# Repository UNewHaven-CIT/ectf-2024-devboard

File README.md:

# UNewHaven 2024 eCTF
### Rev A

This is a daughterboard for the MAX78000FT development board, designed for the 2024 eCTF competition.

This was partially inspired by MITRE's own board design, and from a joke gone too far (the leds are what started it all).

# Features
- As the competition has 3 interconnected boards, this design provisions for side-interconnects
- Independent and chain-able WS2812B LEDs on the top of the board, for some true ectf gaming
- Expandable IO for MAX78000FT board
- SMA monitoring for a selection of voltage lines

# License
This project is licensed under GPLv3.

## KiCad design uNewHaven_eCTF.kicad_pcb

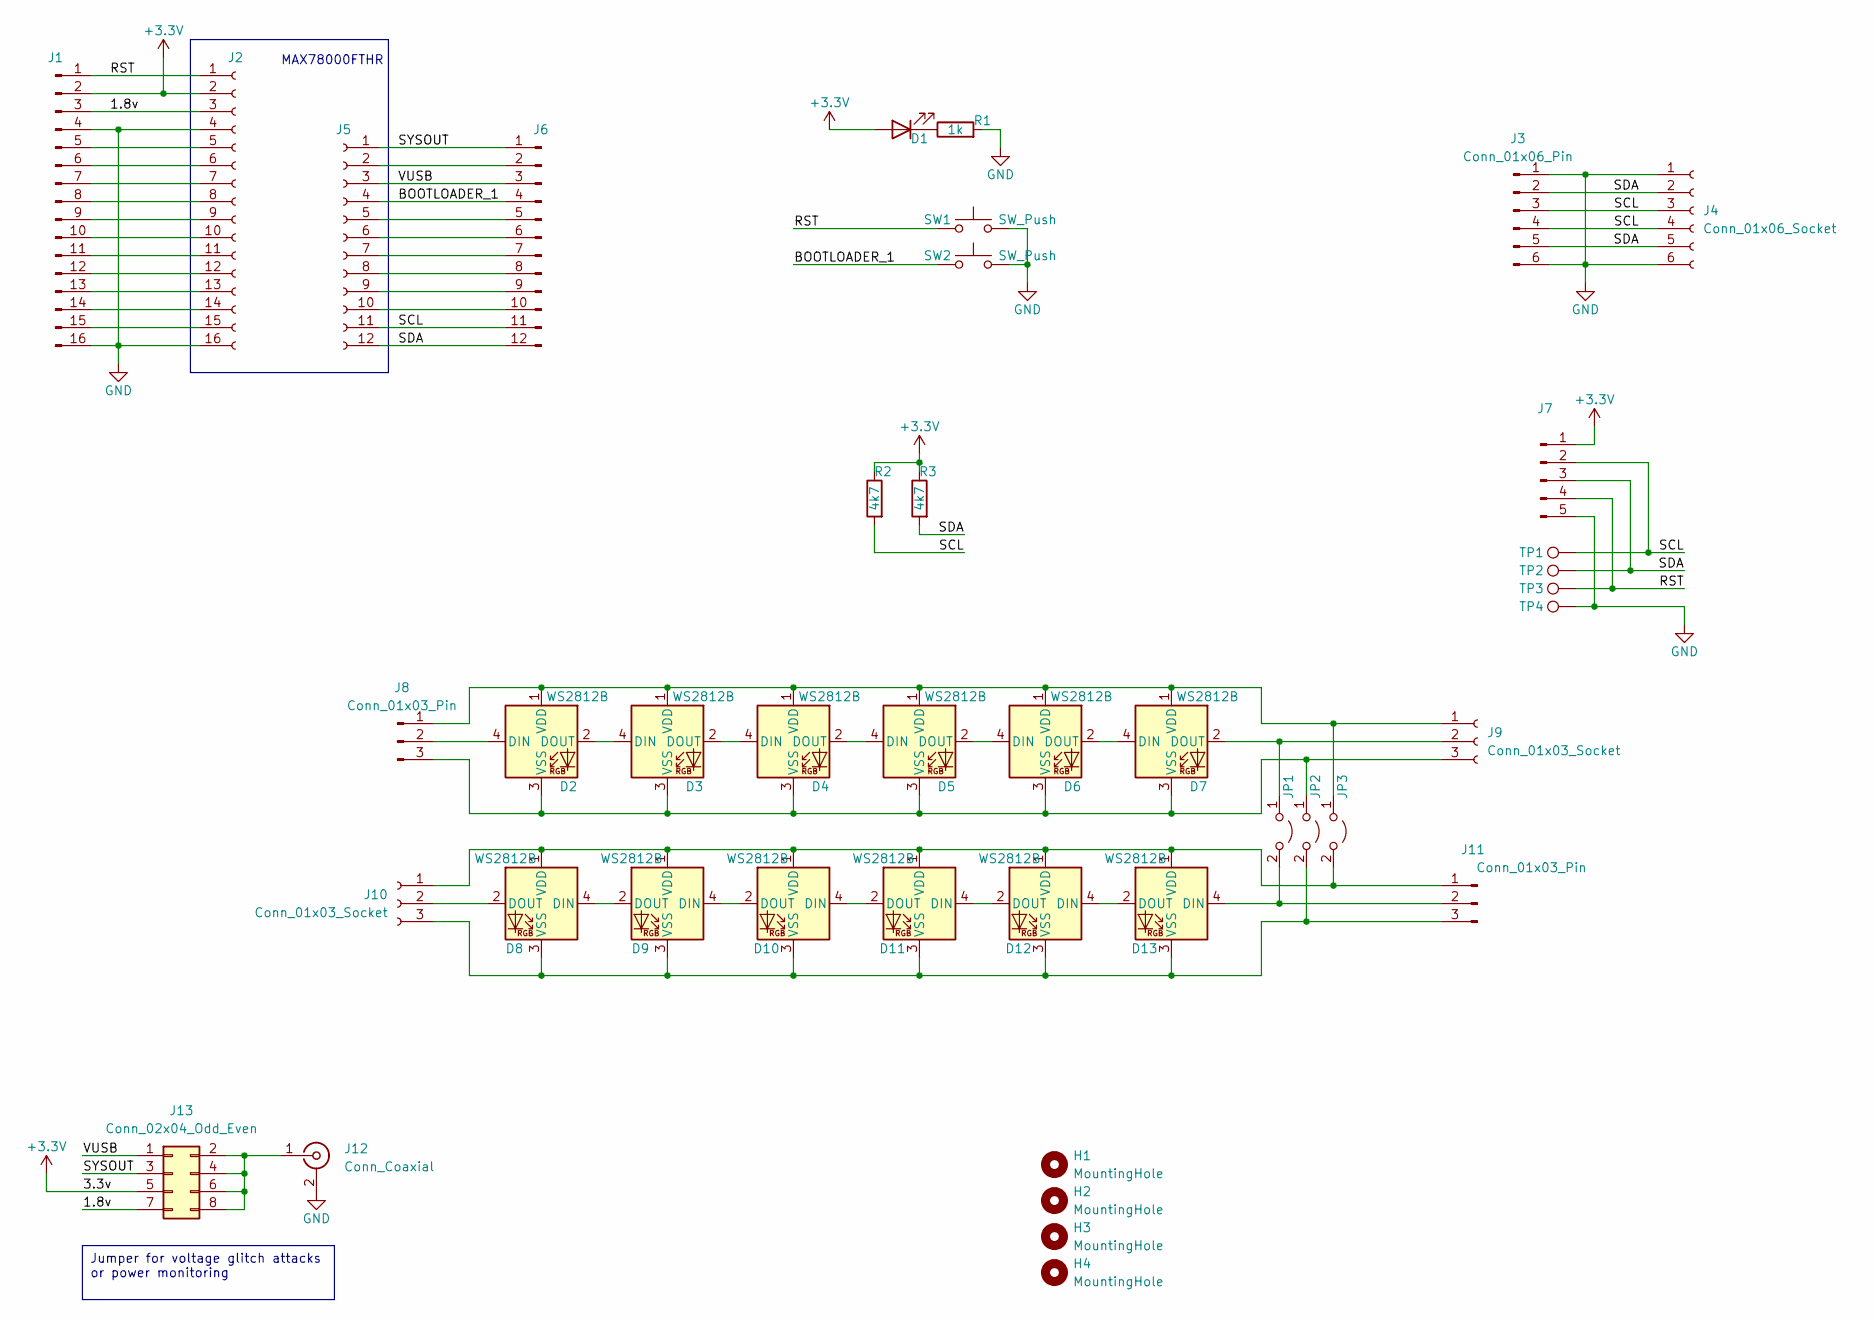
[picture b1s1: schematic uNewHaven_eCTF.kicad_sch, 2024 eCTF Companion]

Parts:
D1: LED; D_1206_3216Metric_Pad1.42x1.75mm_HandSolder
D2, D3, D4, D5, D6, D7, D8, D9, D10, D11, D12, D13: WS2812B; LED_WS2812B_PLCC4_5.0x5.0mm_P3.2mm
H1, H2, H3, H4: MountingHole; MountingHole_3.2mm_M3_DIN965
J1: Conn_01x16_Pin; PinHeader_1x16_P2.54mm_Vertical
J2: Conn_01x16_Socket; PinSocket_1x16_P2.54mm_Vertical
J3: Conn_01x06_Pin; PinHeader_1x06_P2.54mm_Horizontal
J4: Conn_01x06_Socket; PinSocket_1x06_P2.54mm_Horizontal
J5: Conn_01x12_Socket; PinSocket_1x12_P2.54mm_Vertical
J6: Conn_01x12_Pin; PinHeader_1x12_P2.54mm_Vertical
J7: Conn_01x05_Pin; PinHeader_1x05_P2.54mm_Vertical
J8, J11: Conn_01x03_Pin; PinHeader_1x03_P2.54mm_Horizontal
J9, J10: Conn_01x03_Socket; PinSocket_1x03_P2.54mm_Horizontal
J12: Conn_Coaxial; SMA_Amphenol_132291_Vertical
J13: Conn_02x04_Odd_Even; PinHeader_2x04_P2.54mm_Vertical
JP1, JP2, JP3: Jumper_2_Open; R_0805_2012Metric_Pad1.20x1.40mm_HandSolder
R1: 1k; R_0805_2012Metric_Pad1.20x1.40mm_HandSolder
R2, R3: 4k7; R_0805_2012Metric_Pad1.20x1.40mm_HandSolder
SW1, SW2: SW_Push; SW_PUSH_6mm
TP1, TP2, TP3, TP4: TestPoint; TestPoint_Keystone_5005-5009_Compact

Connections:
+3.3V: D1.2 (A), J1.2, J2.2, J7.1, J13.5, R2.1, R3.1
/1.8v: J1.3, J2.3, J13.7
/BOOTLOADER_1: J5.4, J6.4, SW2.1
/RST: J1.1, J2.1, J7.4, SW1.1, TP3.1
/SCL: J3.3, J3.4, J4.3, J4.4, J5.11, J6.11, J7.2, R2.2, TP1.1
/SDA: J3.2, J3.5, J4.2, J4.5, J5.12, J6.12, J7.3, R3.2, TP2.1
/SYSOUT: J5.1, J6.1, J13.3
/VUSB: J5.3, J6.3, J13.1
GND: J1.4, J1.16, J2.4, J2.16, J3.1, J3.6, J4.1, J4.6, J7.5, J12.2 (Ext), R1.2, SW1.2, SW2.2, TP4.1
unnamed: D1.1 (K), R1.1
unnamed: D2.4 (DIN), J8.2
unnamed: D2.2 (DOUT), D3.4 (DIN)
unnamed: D2.1 (VDD), D3.1 (VDD), D4.1 (VDD), D5.1 (VDD), D6.1 (VDD), D7.1 (VDD), J8.1, J9.1, JP3.1 (A)
unnamed: D2.3 (VSS), D3.3 (VSS), D4.3 (VSS), D5.3 (VSS), D6.3 (VSS), D7.3 (VSS), J8.3, J9.3, JP2.1 (A)
unnamed: D3.2 (DOUT), D4.4 (DIN)
unnamed: D4.2 (DOUT), D5.4 (DIN)
unnamed: D5.2 (DOUT), D6.4 (DIN)
unnamed: D6.2 (DOUT), D7.4 (DIN)
unnamed: D7.2 (DOUT), J9.2, JP1.1 (A)
unnamed: D8.4 (DIN), D9.2 (DOUT)
unnamed: D8.2 (DOUT), J10.2
unnamed: D10.4 (DIN), D11.2 (DOUT)
unnamed: D9.4 (DIN), D10.2 (DOUT)
unnamed: D8.1 (VDD), D9.1 (VDD), D10.1 (VDD), D11.1 (VDD), D12.1 (VDD), D13.1 (VDD), J10.1, J11.1, JP3.2 (B)
unnamed: D8.3 (VSS), D9.3 (VSS), D10.3 (VSS), D11.3 (VSS), D12.3 (VSS), D13.3 (VSS), J10.3, J11.3, JP2.2 (B)
unnamed: D11.4 (DIN), D12.2 (DOUT)
unnamed: D12.4 (DIN), D13.2 (DOUT)
unnamed: D13.4 (DIN), J11.2, JP1.2 (B)
unnamed: J1.5, J2.5
unnamed: J1.6, J2.6
unnamed: J1.7, J2.7
unnamed: J1.8, J2.8
unnamed: J1.9, J2.9
unnamed: J1.10, J2.10
unnamed: J1.11, J2.11
unnamed: J1.12, J2.12
unnamed: J1.13, J2.13
unnamed: J1.14, J2.14
unnamed: J1.15, J2.15
unnamed: J5.2, J6.2
unnamed: J5.5, J6.5
unnamed: J5.6, J6.6
unnamed: J5.7, J6.7
unnamed: J5.8, J6.8
unnamed: J5.9, J6.9
unnamed: J5.10, J6.10
unnamed: J12.1 (In), J13.2, J13.4, J13.6, J13.8

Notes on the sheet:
Jumper for voltage glitch attacks or power monitoring
MAX78000FTHR

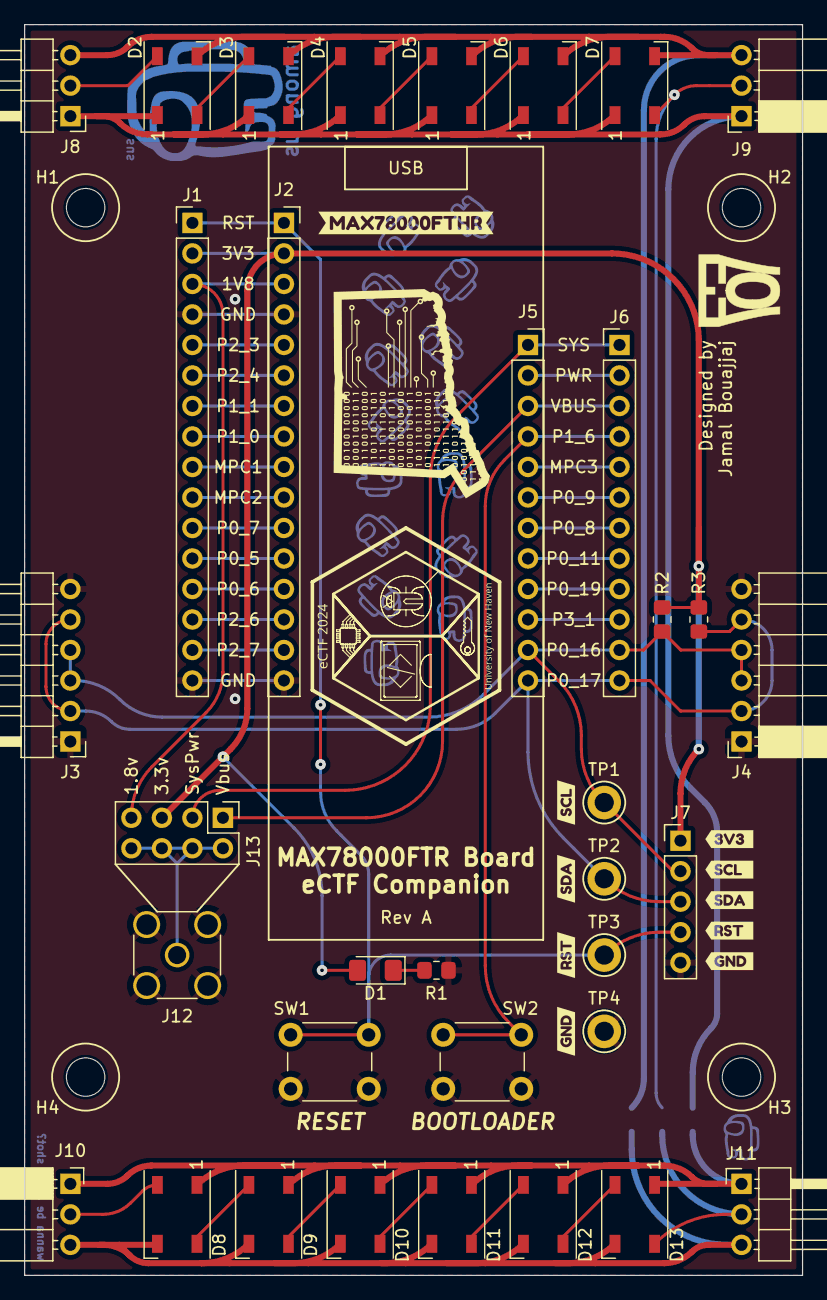
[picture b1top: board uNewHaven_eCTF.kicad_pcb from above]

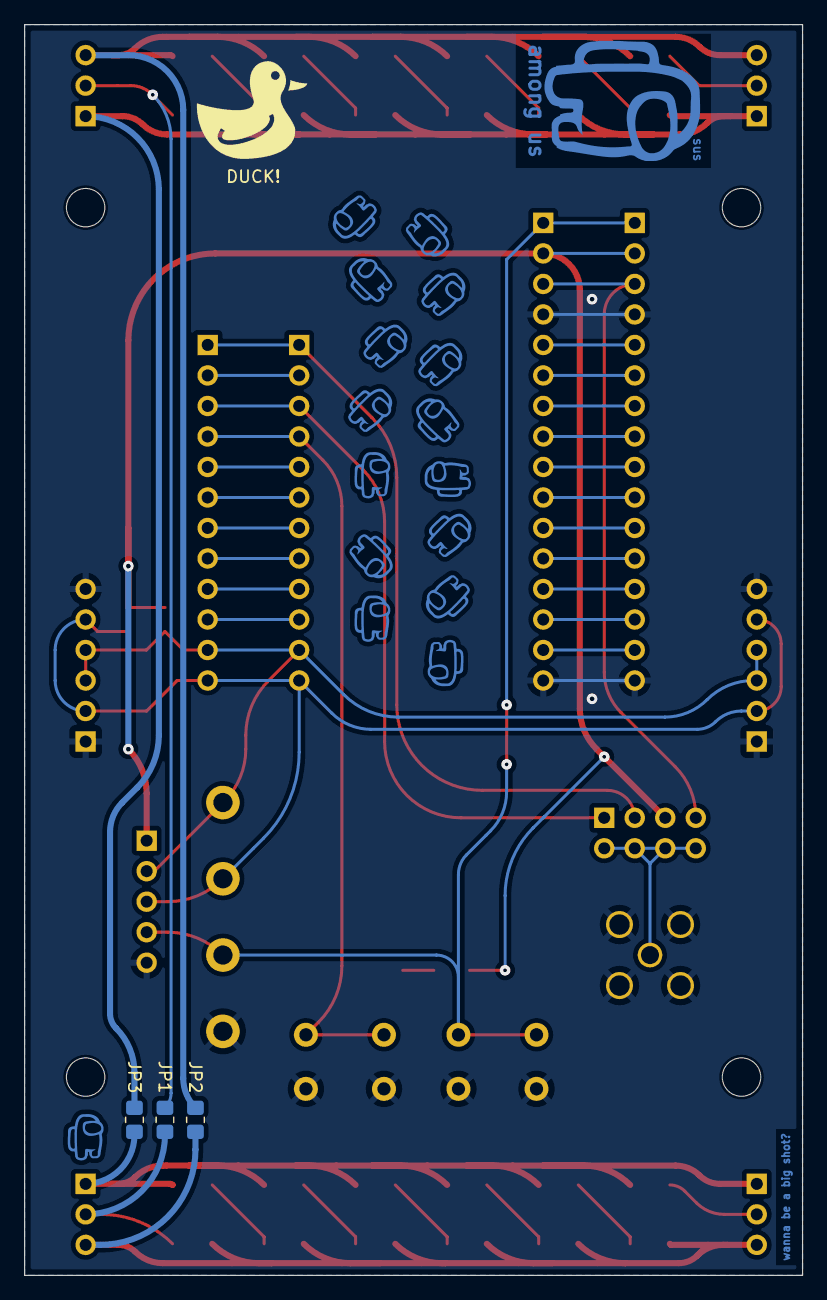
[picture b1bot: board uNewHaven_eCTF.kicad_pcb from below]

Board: 2 copper layers, 64.8 x 104.1 mm, 52 parts (3 on the bottom side), 47 nets.

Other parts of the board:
kibuzzard-65C1A1E7: G***; kibuzzard-65C1A1E7
kibuzzard-65C1A1F1: G***; kibuzzard-65C1A1F1
kibuzzard-65C1A1F5: G***; kibuzzard-65C1A1F5
kibuzzard-65C1A1FA: G***; kibuzzard-65C1A1FA
kibuzzard-65C1A1FF: G***; kibuzzard-65C1A1FF
kibuzzard-65C19DC0: G***; kibuzzard-65C19DC0
kibuzzard-65C19DCD: G***; kibuzzard-65C19DCD
kibuzzard-65C19DD2: G***; kibuzzard-65C19DD2
kibuzzard-65C19DD8: G***; kibuzzard-65C19DD8
kibuzzard-65C19E6E: G***; kibuzzard-65C19E6E
